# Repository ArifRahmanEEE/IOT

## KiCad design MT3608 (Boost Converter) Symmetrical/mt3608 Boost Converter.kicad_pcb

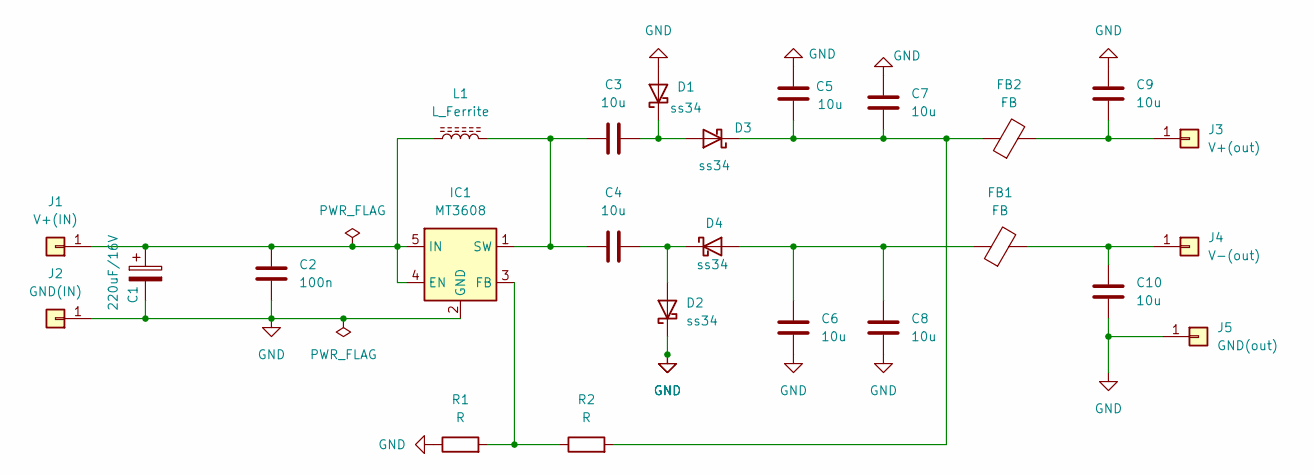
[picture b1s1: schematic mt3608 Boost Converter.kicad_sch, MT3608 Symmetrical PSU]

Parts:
C1: 220uF/16V; CP_Elec_8x10
C2: 100n; C_1206_3216Metric
C3, C4, C5, C6, C7, C8, C9, C10: 10u; C_1206_3216Metric
D1, D2, D3, D4: ss34; D_SMA-SMB_Universal_Handsoldering
FB1, FB2: FB; L_Axial_L5.3mm_D2.2mm_P2.54mm_Vertical_Vishay_IM-1
IC1: MT3608; SOT-23-6
J1: V+(IN); SolderWire-0.5sqmm_1x01_D0.9mm_OD2.3mm
J2: GND(IN); SolderWire-0.5sqmm_1x01_D0.9mm_OD2.3mm
J3: V+(out); SolderWire-0.5sqmm_1x01_D0.9mm_OD2.3mm
J4: V-(out); SolderWire-0.5sqmm_1x01_D0.9mm_OD2.3mm
J5: GND(out); SolderWire-0.5sqmm_1x01_D0.9mm_OD2.3mm
L1: L_Ferrite; L_Taiyo-Yuden_NR-60xx_HandSoldering
R1, R2: R; R_1206_3216Metric

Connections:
GND: C1.2, C2.2, C5.2, C6.1, C7.2, C8.1, C9.2, C10.1, D1.2 (A), D2.1 (K), IC1.2 (GND), J2.1, J5.1, R1.1
unnamed: C3.2, D1.1 (K), D3.2 (A)
unnamed: C4.2, D2.2 (A), D4.1 (K)
unnamed: C5.1, C7.1, D3.1 (K), FB2.1, R2.2
unnamed: C6.2, C8.2, D4.2 (A), FB1.1
unnamed: C1.1, C2.1, IC1.4 (EN), IC1.5 (IN), J1.1, L1.1
unnamed: IC1.3 (FB), R1.2, R2.1
unnamed: C3.1, C4.1, IC1.1 (SW), L1.2
unnamed: C9.1, FB2.2, J3.1
unnamed: C10.2, FB1.2, J4.1

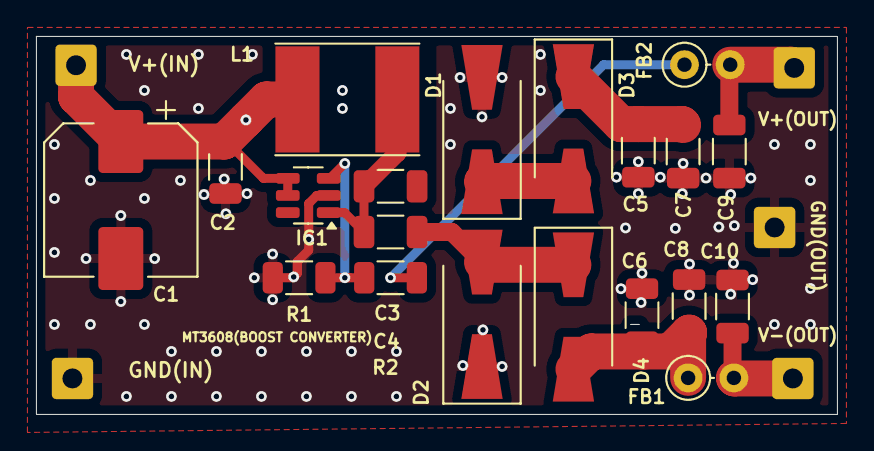
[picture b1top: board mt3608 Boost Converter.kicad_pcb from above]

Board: 2 copper layers, 44.5 x 21.0 mm, 25 parts (0 on the bottom side), 10 nets.

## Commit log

2024-12-11 Create PCB
